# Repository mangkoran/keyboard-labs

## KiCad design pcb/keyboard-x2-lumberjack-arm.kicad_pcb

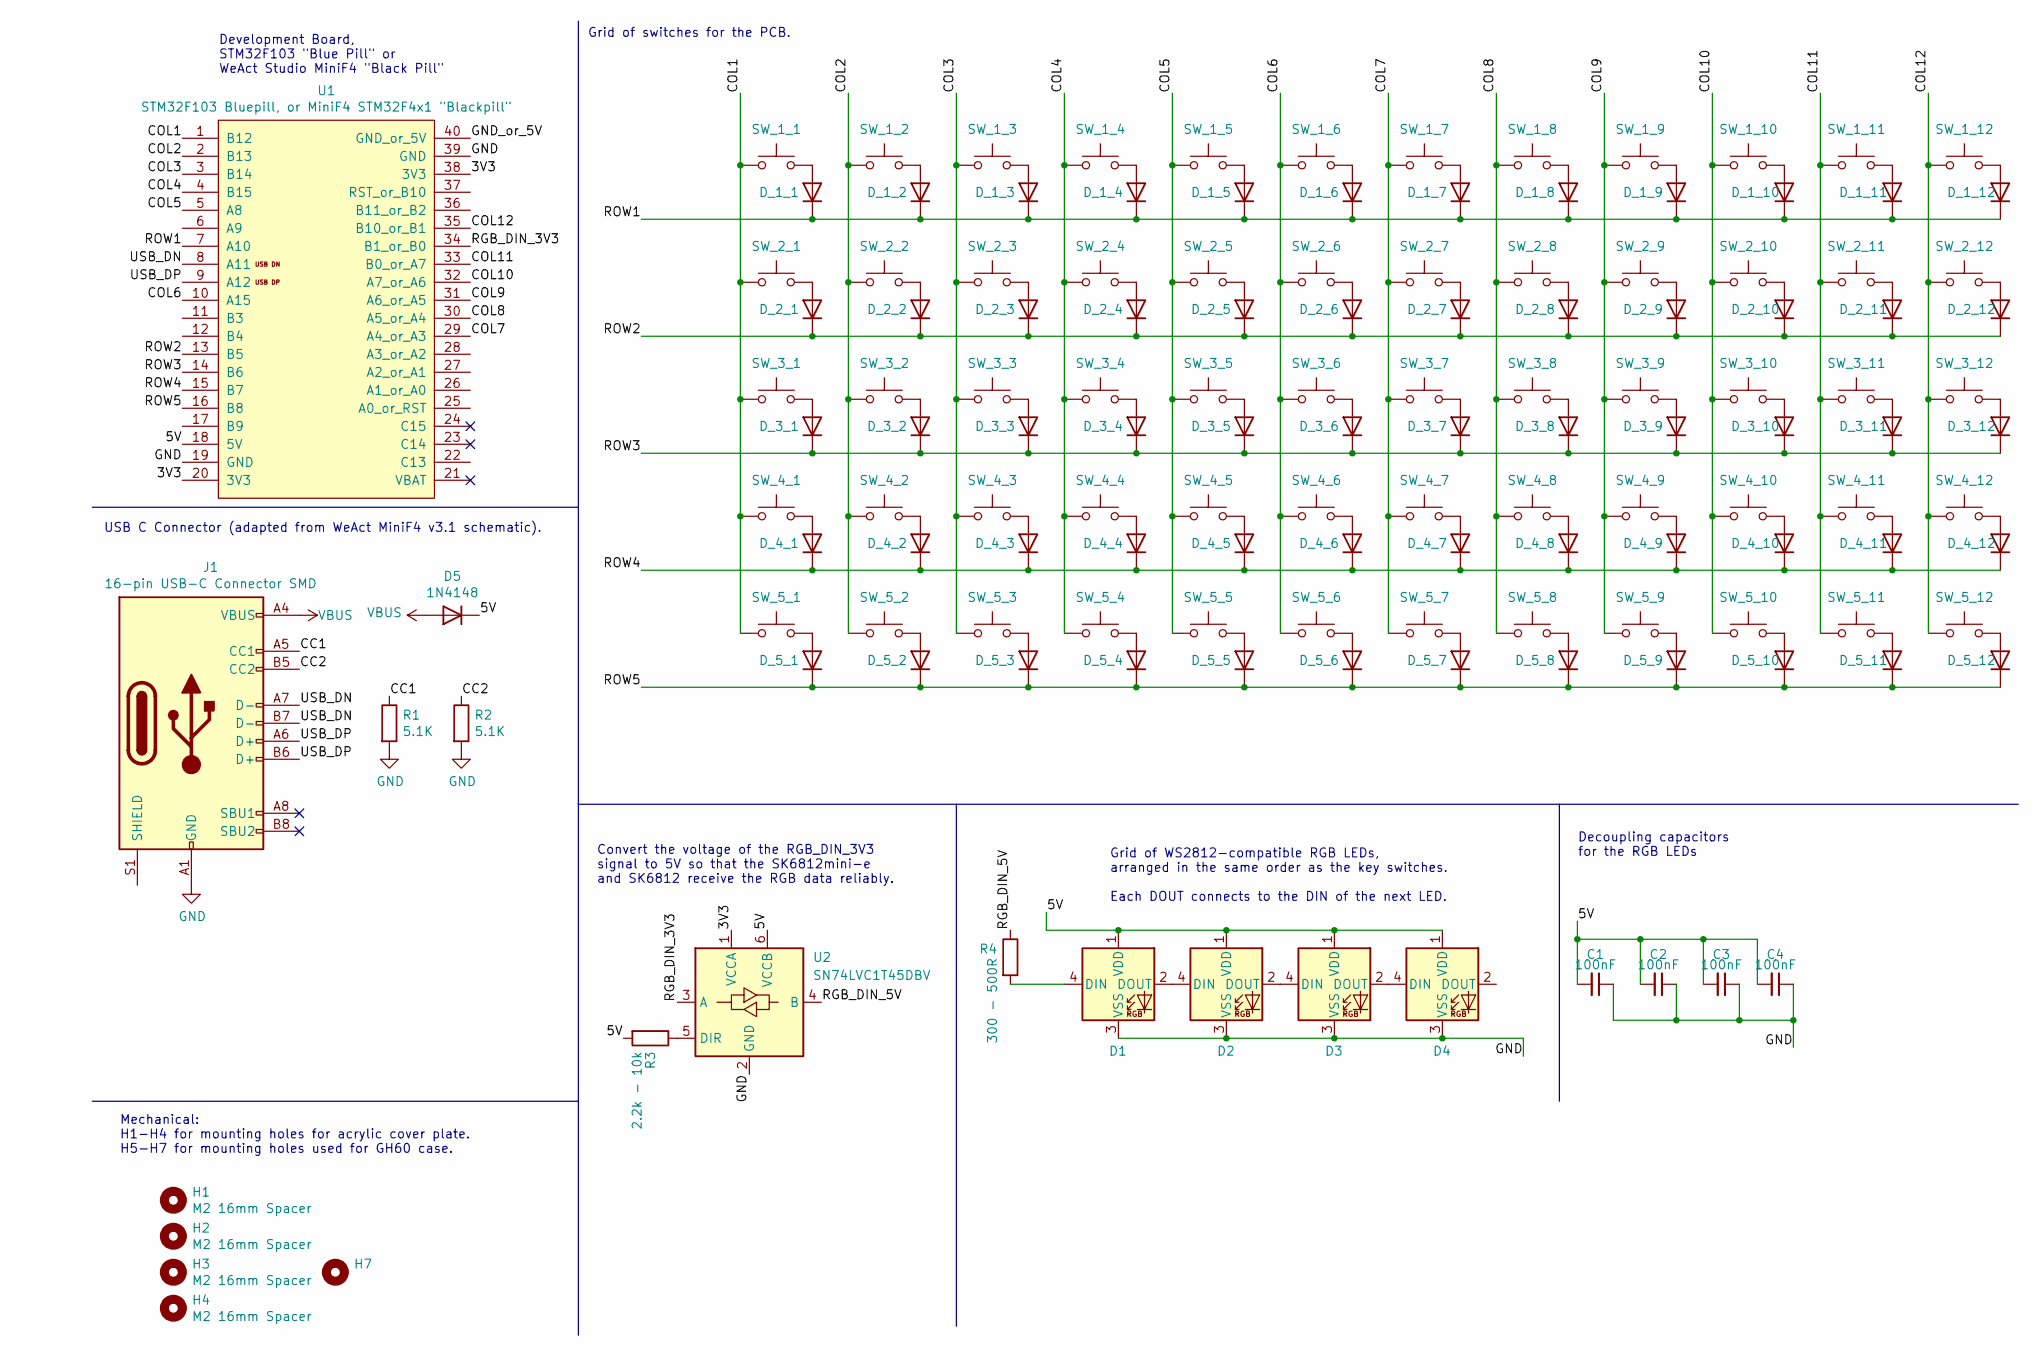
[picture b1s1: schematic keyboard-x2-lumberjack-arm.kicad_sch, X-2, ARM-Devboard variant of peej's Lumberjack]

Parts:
C1, C2, C3, C4: 100nF; C_0805_2012Metric_Pad1.18x1.45mm_HandSolder_Dual
D1, D2, D3, D4: SK6812; LED_WS2812B_PLCC4_5.0x5.0mm_P3.2mm
D5: 1N4148; Diode-dual
D_1_1, D_1_2, D_1_3, D_1_4, D_1_5, D_1_6, D_1_7, D_1_8, D_1_9, D_1_10, D_1_11, D_1_12, D_2_1, D_2_2, D_2_3, D_2_4, D_2_5, D_2_6, D_2_7, D_2_8, D_2_9, D_2_10, D_2_11, D_2_12, D_3_1, D_3_2, D_3_3, D_3_4, D_3_5, D_3_6, D_3_7, D_3_8, D_3_9, D_3_10, D_3_11, D_3_12, D_4_1, D_4_2, D_4_3, D_4_4, D_4_5, D_4_6, D_4_7, D_4_8, D_4_9, D_4_10, D_4_11, D_4_12, D_5_1, D_5_2, D_5_3, D_5_4, D_5_5, D_5_6, D_5_7, D_5_8, D_5_9, D_5_10, D_5_11, D_5_12: 1N4148; Diode-dual
H1, H2, H3, H4: M2 16mm Spacer; MountingHole_2.2mm_M2_DIN965_Pad
H7: H_M2_Spacer_Hole
J1: 16-pin USB-C Connector SMD; USB_C_Receptacle_XKB_U262-16XN-4BVC11
R1, R2: 5.1K; Resistor-Hybrid
R3: 2.2k - 10k; Resistor-Hybrid
R4: 300 - 500R; Resistor-Hybrid
SW_1_1, SW_1_2, SW_1_3, SW_1_4, SW_1_5, SW_1_6, SW_1_7, SW_1_8, SW_1_9, SW_1_10, SW_1_11, SW_1_12, SW_2_1, SW_2_2, SW_2_3, SW_2_4, SW_2_5, SW_2_6, SW_2_7, SW_2_8, SW_2_9, SW_2_10, SW_2_11, SW_2_12, SW_3_1, SW_3_2, SW_3_3, SW_3_4, SW_3_5, SW_3_6, SW_3_7, SW_3_8, SW_3_9, SW_3_10, SW_3_11, SW_3_12, SW_4_1, SW_4_2, SW_4_3, SW_4_4, SW_4_5, SW_4_6, SW_4_7, SW_4_8, SW_4_9, SW_4_10, SW_4_11, SW_4_12, SW_5_1, SW_5_2, SW_5_3, SW_5_4, SW_5_5, SW_5_6, SW_5_7, SW_5_8, SW_5_9, SW_5_10, SW_5_11, SW_5_12: MX Hotswap; MXOnly-1U-Hotswap-180
U1: STM32F103 Bluepill, or MiniF4 STM32F4x1 "Blackpil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; DIP-40_W15.24mm_Socket
U2: SN74LVC1T45DBV; SOT-23-6_Handsoldering

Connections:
/3V3: U1.20 (3V3), U1.38 (3V3), U2.1 (VCCA)
/5V: C1.2, C2.2, C3.2, C4.2, D1.1 (VDD), D2.1 (VDD), D3.1 (VDD), D4.1 (VDD), D5.1 (K), R3.2, U1.18 (5V), U2.6 (VCCB)
/CC1: J1.A5 (CC1), R1.1
/CC2: J1.B5 (CC2), R2.1
/COL1: SW_1_1.1, SW_2_1.1, SW_3_1.1, SW_4_1.1, SW_5_1.1, U1.1 (B12)
/COL2: SW_1_2.1, SW_2_2.1, SW_3_2.1, SW_4_2.1, SW_5_2.1, U1.2 (B13)
/COL3: SW_1_3.1, SW_2_3.1, SW_3_3.1, SW_4_3.1, SW_5_3.1, U1.3 (B14)
/COL4: SW_1_4.1, SW_2_4.1, SW_3_4.1, SW_4_4.1, SW_5_4.1, U1.4 (B15)
/COL5: SW_1_5.1, SW_2_5.1, SW_3_5.1, SW_4_5.1, SW_5_5.1, U1.5 (A8)
/COL6: SW_1_6.1, SW_2_6.1, SW_3_6.1, SW_4_6.1, SW_5_6.1, U1.10 (A15)
/COL7: SW_1_7.1, SW_2_7.1, SW_3_7.1, SW_4_7.1, SW_5_7.1, U1.29 (A4_or_A3)
/COL8: SW_1_8.1, SW_2_8.1, SW_3_8.1, SW_4_8.1, SW_5_8.1, U1.30 (A5_or_A4)
/COL9: SW_1_9.1, SW_2_9.1, SW_3_9.1, SW_4_9.1, SW_5_9.1, U1.31 (A6_or_A5)
/COL10: SW_1_10.1, SW_2_10.1, SW_3_10.1, SW_4_10.1, SW_5_10.1, U1.32 (A7_or_A6)
/COL11: SW_1_11.1, SW_2_11.1, SW_3_11.1, SW_4_11.1, SW_5_11.1, U1.33 (B0_or_A7)
/COL12: SW_1_12.1, SW_2_12.1, SW_3_12.1, SW_4_12.1, SW_5_12.1, U1.35 (B10_or_B1)
/GND_or_5V: U1.40 (GND_or_5V)
/RGB_DIN_3V3: U1.34 (B1_or_B0), U2.3 (A)
/RGB_DIN_5V: R4.1, U2.4 (B)
/ROW1: D_1_1.1 (K), D_1_2.1 (K), D_1_3.1 (K), D_1_4.1 (K), D_1_5.1 (K), D_1_6.1 (K), D_1_7.1 (K), D_1_8.1 (K), D_1_9.1 (K), D_1_10.1 (K), D_1_11.1 (K), D_1_12.1 (K), U1.7 (A10)
/ROW2: D_2_1.1 (K), D_2_2.1 (K), D_2_3.1 (K), D_2_4.1 (K), D_2_5.1 (K), D_2_6.1 (K), D_2_7.1 (K), D_2_8.1 (K), D_2_9.1 (K), D_2_10.1 (K), D_2_11.1 (K), D_2_12.1 (K), U1.13 (B5)
/ROW3: D_3_1.1 (K), D_3_2.1 (K), D_3_3.1 (K), D_3_4.1 (K), D_3_5.1 (K), D_3_6.1 (K), D_3_7.1 (K), D_3_8.1 (K), D_3_9.1 (K), D_3_10.1 (K), D_3_11.1 (K), D_3_12.1 (K), U1.14 (B6)
/ROW4: D_4_1.1 (K), D_4_2.1 (K), D_4_3.1 (K), D_4_4.1 (K), D_4_5.1 (K), D_4_6.1 (K), D_4_7.1 (K), D_4_8.1 (K), D_4_9.1 (K), D_4_10.1 (K), D_4_11.1 (K), D_4_12.1 (K), U1.15 (B7)
/ROW5: D_5_1.1 (K), D_5_2.1 (K), D_5_3.1 (K), D_5_4.1 (K), D_5_5.1 (K), D_5_6.1 (K), D_5_7.1 (K), D_5_8.1 (K), D_5_9.1 (K), D_5_10.1 (K), D_5_11.1 (K), D_5_12.1 (K), U1.16 (B8)
/USB_DN: J1.A7 (D-), J1.B7 (D-), U1.8 (A11)
/USB_DP: J1.A6 (D+), J1.B6 (D+), U1.9 (A12)
GND: C1.1, C2.1, C3.1, C4.1, D1.3 (VSS), D2.3 (VSS), D3.3 (VSS), D4.3 (VSS), J1.A1 (GND), J1.A12 (GND), J1.B1 (GND), J1.B12 (GND), R1.2, R2.2, U1.19 (GND), U1.39 (GND), U2.2 (GND)
unnamed: D1.2 (DOUT), D2.4 (DIN)
unnamed: D1.4 (DIN), R4.2
unnamed: D2.2 (DOUT), D3.4 (DIN)
unnamed: D3.2 (DOUT), D4.4 (DIN)
unnamed: D_1_1.2 (A), SW_1_1.2
unnamed: D_1_2.2 (A), SW_1_2.2
unnamed: D_1_3.2 (A), SW_1_3.2
unnamed: D_1_4.2 (A), SW_1_4.2
unnamed: D_1_5.2 (A), SW_1_5.2
unnamed: D_1_6.2 (A), SW_1_6.2
unnamed: D_1_7.2 (A), SW_1_7.2
unnamed: D_1_8.2 (A), SW_1_8.2
unnamed: D_1_9.2 (A), SW_1_9.2
unnamed: D_1_10.2 (A), SW_1_10.2
unnamed: D_1_11.2 (A), SW_1_11.2
unnamed: D_1_12.2 (A), SW_1_12.2
unnamed: D_2_1.2 (A), SW_2_1.2
unnamed: D_2_2.2 (A), SW_2_2.2
unnamed: D_2_3.2 (A), SW_2_3.2
unnamed: D_2_4.2 (A), SW_2_4.2
unnamed: D_2_5.2 (A), SW_2_5.2
unnamed: D_2_6.2 (A), SW_2_6.2
unnamed: D_2_7.2 (A), SW_2_7.2
unnamed: D_2_8.2 (A), SW_2_8.2
unnamed: D_2_9.2 (A), SW_2_9.2
unnamed: D_2_10.2 (A), SW_2_10.2
unnamed: D_2_11.2 (A), SW_2_11.2
unnamed: D_2_12.2 (A), SW_2_12.2
unnamed: D_3_1.2 (A), SW_3_1.2
unnamed: D_3_2.2 (A), SW_3_2.2
unnamed: D_3_3.2 (A), SW_3_3.2
unnamed: D_3_4.2 (A), SW_3_4.2
unnamed: D_3_5.2 (A), SW_3_5.2
unnamed: D_3_6.2 (A), SW_3_6.2
unnamed: D_3_7.2 (A), SW_3_7.2
unnamed: D_3_8.2 (A), SW_3_8.2
unnamed: D_3_9.2 (A), SW_3_9.2
unnamed: D_3_10.2 (A), SW_3_10.2
unnamed: D_3_11.2 (A), SW_3_11.2
unnamed: D_3_12.2 (A), SW_3_12.2
unnamed: D_4_1.2 (A), SW_4_1.2
unnamed: D_4_2.2 (A), SW_4_2.2
unnamed: D_4_3.2 (A), SW_4_3.2
unnamed: D_4_4.2 (A), SW_4_4.2
unnamed: D_4_5.2 (A), SW_4_5.2
unnamed: D_4_6.2 (A), SW_4_6.2
unnamed: D_4_7.2 (A), SW_4_7.2
unnamed: D_4_8.2 (A), SW_4_8.2
unnamed: D_4_9.2 (A), SW_4_9.2
unnamed: D_4_10.2 (A), SW_4_10.2
unnamed: D_4_11.2 (A), SW_4_11.2
unnamed: D_4_12.2 (A), SW_4_12.2
unnamed: D_5_1.2 (A), SW_5_1.2
unnamed: D_5_2.2 (A), SW_5_2.2
unnamed: D_5_3.2 (A), SW_5_3.2
unnamed: D_5_4.2 (A), SW_5_4.2
unnamed: D_5_5.2 (A), SW_5_5.2
unnamed: D_5_6.2 (A), SW_5_6.2
unnamed: D_5_7.2 (A), SW_5_7.2
unnamed: D_5_8.2 (A), SW_5_8.2
unnamed: D_5_9.2 (A), SW_5_9.2
unnamed: D_5_10.2 (A), SW_5_10.2
unnamed: D_5_11.2 (A), SW_5_11.2
unnamed: D_5_12.2 (A), SW_5_12.2
unnamed: R3.1, U2.5 (DIR)
VBUS: D5.2 (A), J1.A4 (VBUS), J1.A9 (VBUS), J1.B4 (VBUS), J1.B9 (VBUS)

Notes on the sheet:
Convert the voltage of the RGB_DIN_3V3 signal to 5V so that the SK6812mini-e and SK6812 receive the RGB data reliably.
Mechanical: H1-H4 for mounting holes for acrylic cover plate. H5-H7 for mounting holes used for GH60 case.
USB C Connector (adapted from WeAct MiniF4 v3.1 schematic).
Development Board, STM32F103 "Blue Pill" or WeAct Studio MiniF4 "Black Pill"
Grid of WS2812-compatible RGB LEDs, arranged in the same order as the key switches. Each DOUT connects to the DIN of the next LED.
Decoupling capacitors for the RGB LEDs
Grid of switches for the PCB.

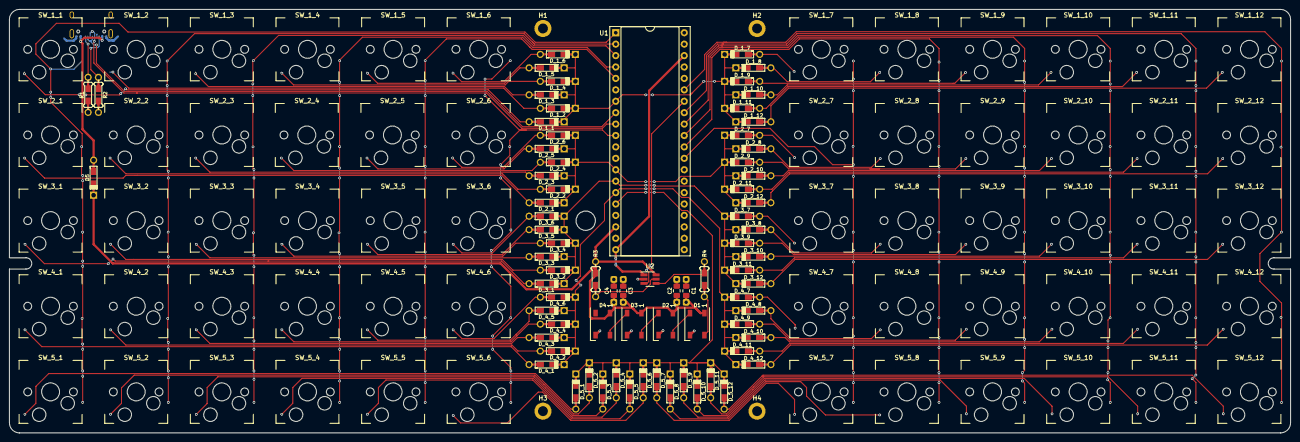
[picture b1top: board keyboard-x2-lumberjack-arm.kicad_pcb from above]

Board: 2 copper layers, 285.0 x 94.2 mm, 141 parts (1 on the bottom side), 92 nets.

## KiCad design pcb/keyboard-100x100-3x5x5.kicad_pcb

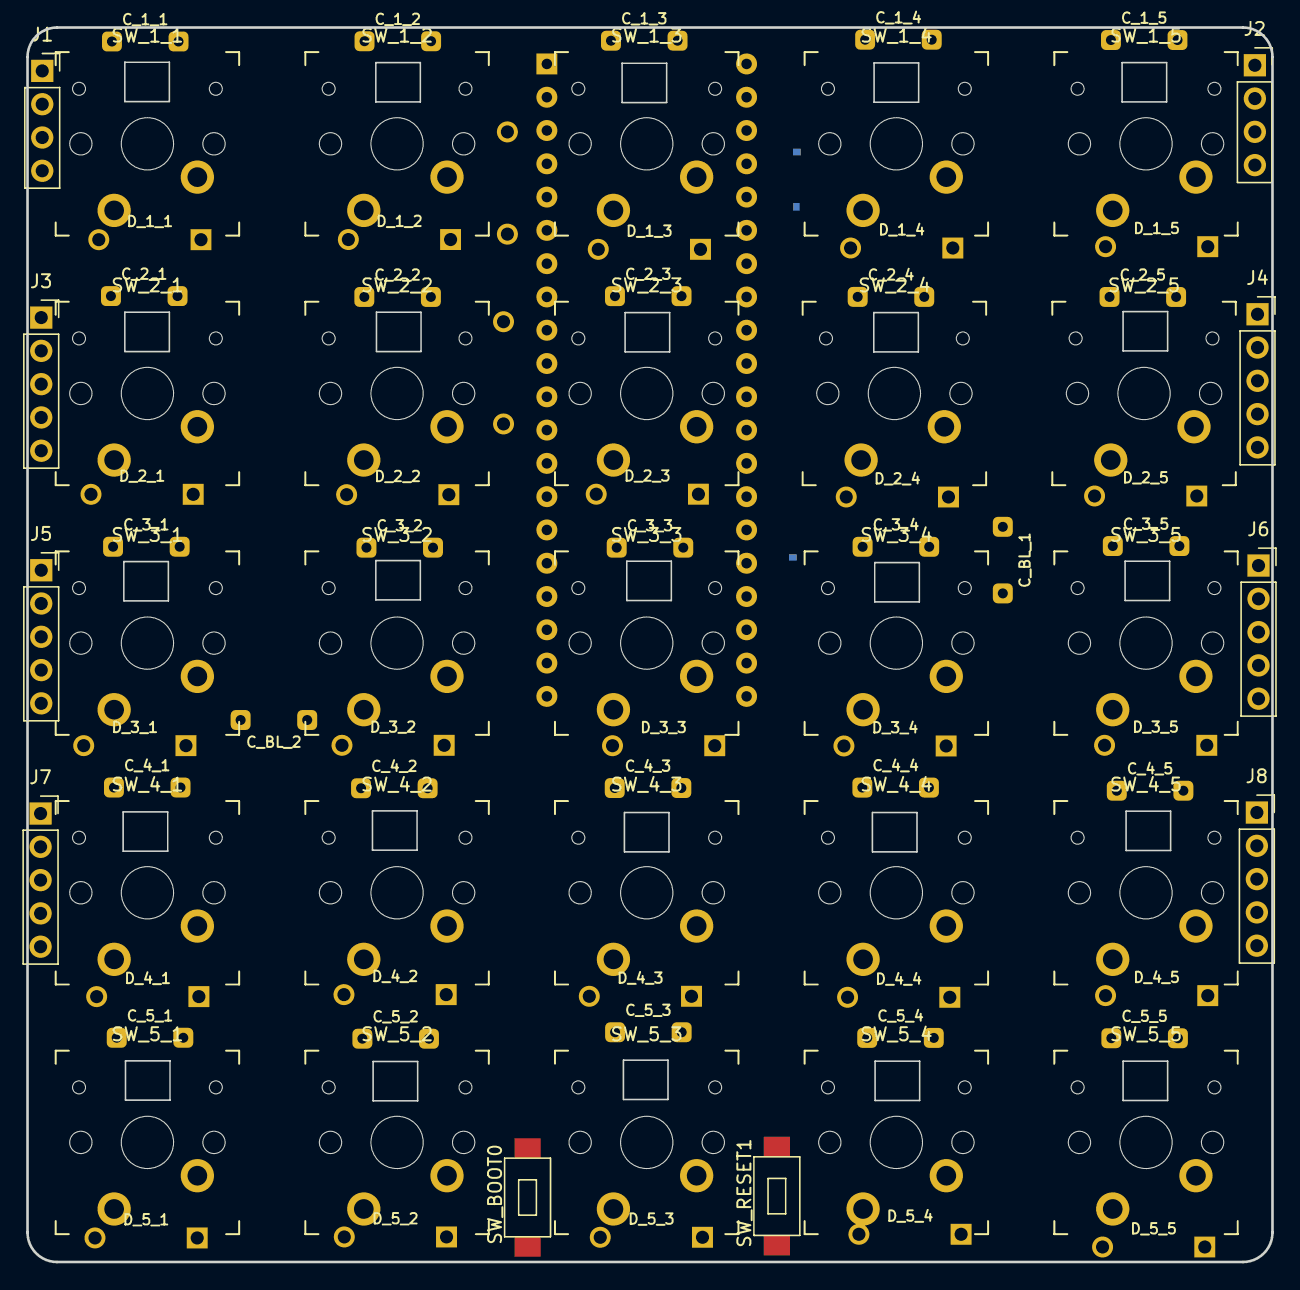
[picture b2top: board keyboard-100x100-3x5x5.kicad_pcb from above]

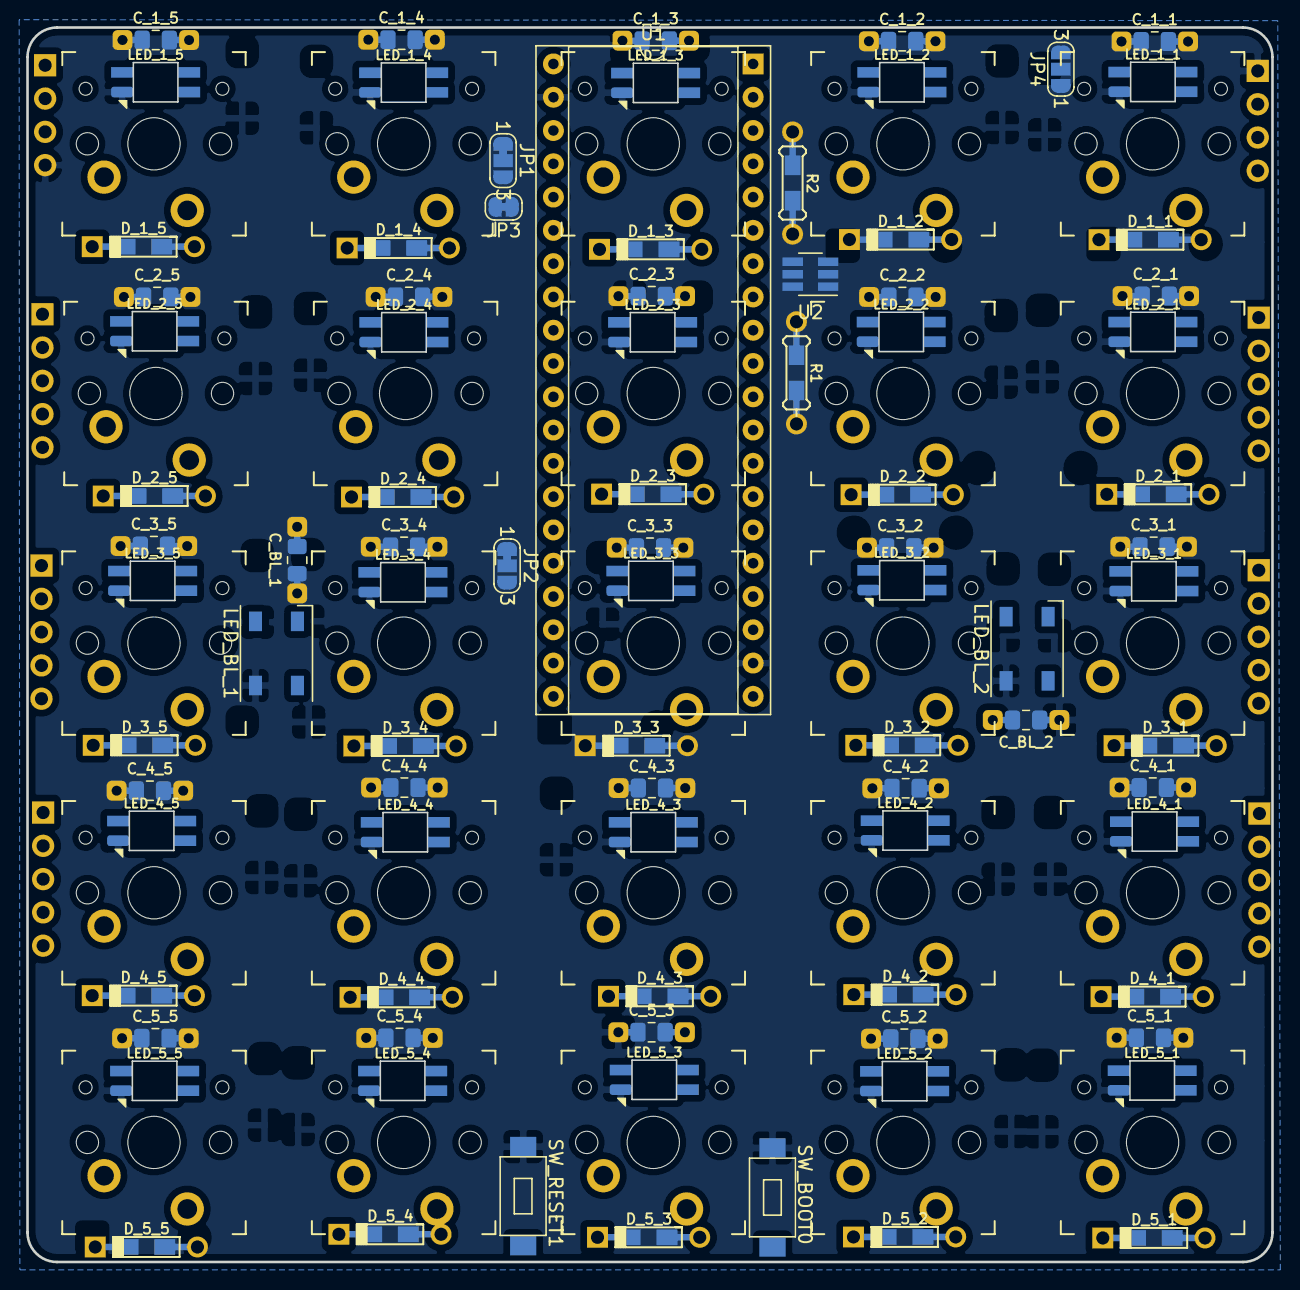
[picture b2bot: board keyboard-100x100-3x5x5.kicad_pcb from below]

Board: 2 copper layers, 95.0 x 94.2 mm, 126 parts (86 on the bottom side), 88 nets, no tracks yet.

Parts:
C_1_1, C_1_2, C_1_3, C_1_4, C_1_5, C_2_1, C_2_2, C_2_3, C_2_4, C_2_5, C_3_1, C_3_2, C_3_3, C_3_4, C_3_5, C_4_1, C_4_2, C_4_3, C_4_4, C_4_5, C_5_1, C_5_2, C_5_3, C_5_4, C_5_5: 100nF; C_0805_2012Metric_Pad1.18x1.45mm_HandSolder_Dual
C_BL_1, C_BL_2: 100nF; C_0805_2012Metric_Pad1.18x1.45mm_HandSolder_Dual
D_1_1, D_1_2, D_1_3, D_1_4, D_1_5, D_2_1, D_2_2, D_2_3, D_2_4, D_2_5, D_3_1, D_3_2, D_3_3, D_3_4, D_3_5, D_4_1, D_4_2, D_4_3, D_4_4, D_4_5, D_5_1, D_5_2, D_5_3, D_5_4, D_5_5: D; Diode-dual
H1, H2, H3, H4: MountingHole; Bumpon_3M_F0502
J1, J2: Conn_01x04_Female; PinSocket_1x04_P2.54mm_Vertical
J3, J4, J5, J6, J7, J8: Conn_01x05_Female; PinSocket_1x05_P2.54mm_Vertical
JP1, JP2: SolderJumper_3_Bridged12; SolderJumper-3_P1.3mm_Bridged12_RoundedPad1.0x1.5mm_NumberL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
JP3: SolderJumper_2_Bridged; SolderJumper-2_P1.3mm_Bridged_RoundedPad1.0x1.5mm
JP4: SolderJumper_3_Open; SolderJumper-3_P1.3mm_Open_RoundedPad1.0x1.5mm_NumberLabels
LED_1_1, LED_1_2, LED_1_3, LED_1_4, LED_1_5, LED_2_1, LED_2_2, LED_2_3, LED_2_4, LED_2_5, LED_3_1, LED_3_2, LED_3_3, LED_3_4, LED_3_5, LED_4_1, LED_4_2, LED_4_3, LED_4_4, LED_4_5, LED_5_1, LED_5_2, LED_5_3, LED_5_4, LED_5_5: WS2812B; SK6812-MINI-E
LED_BL_1, LED_BL_2: WS2812B; LED_SK6812_PLCC4_5.0x5.0mm_P3.2mm
R1: 2.2k - 10k; Resistor-Hybrid
R2: 300 - 500R; Resistor-Hybrid
SW_1_1, SW_1_2, SW_1_3, SW_1_4, SW_1_5, SW_2_1, SW_2_2, SW_2_3, SW_2_4, SW_2_5, SW_3_1, SW_3_2, SW_3_3, SW_3_4, SW_3_5, SW_4_1, SW_4_2, SW_4_3, SW_4_4, SW_4_5, SW_5_1, SW_5_2, SW_5_3, SW_5_4, SW_5_5: SW_Push; SW_MX_SK6812mini-e
SW_BOOT0: SW_Push; SW_Push_SPST_3x6mm
SW_RESET1: SW_Push; SW_Push_SPST_3x6mm
U1: BluePill_or_MiniF4_DIP40; DIP-40_W15.24mm_Socket_Flipped
U2: SN74LVC1T45DBV; SOT-23-6_Handsoldering

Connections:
/3V3: U1.20, U1.38, U2.1
/5V: C_1_1.2, C_1_2.2, C_1_3.2, C_1_4.2, C_1_5.2, C_2_1.2, C_2_2.2, C_2_3.2, C_2_4.2, C_2_5.2, C_3_1.2, C_3_2.2, C_3_3.2, C_3_4.2, C_3_5.2, C_4_1.2, C_4_2.2, C_4_3.2, C_4_4.2, C_4_5.2, C_5_1.2, C_5_2.2, C_5_3.2, C_5_4.2, C_5_5.2, C_BL_1.2, C_BL_2.2, J1.2, J2.3, LED_1_1.1, LED_1_2.1, LED_1_3.1, LED_1_4.1, LED_1_5.1, LED_2_1.1, LED_2_2.1, LED_2_3.1, LED_2_4.1, LED_2_5.1, LED_3_1.1, LED_3_2.1, LED_3_3.1, LED_3_4.1, LED_3_5.1, LED_4_1.1, LED_4_2.1, LED_4_3.1, LED_4_4.1, LED_4_5.1, LED_5_1.1, LED_5_2.1, LED_5_3.1, LED_5_4.1, LED_5_5.1, LED_BL_1.1, LED_BL_2.1, R1.2, U1.18, U2.6
/BOOT0: JP3.2, SW_BOOT0.1
/COL1: J5.5, J8.1, SW_1_1.1, SW_2_1.1, SW_3_1.1, SW_4_1.1, SW_5_1.1, U1.10
/COL2: J5.4, J8.2, SW_1_2.1, SW_2_2.1, SW_3_2.1, SW_4_2.1, SW_5_2.1, U1.29
/COL3: J5.3, J8.3, SW_1_3.1, SW_2_3.1, SW_3_3.1, SW_4_3.1, SW_5_3.1, U1.30
/COL4: J5.2, J8.4, SW_1_4.1, SW_2_4.1, SW_3_4.1, SW_4_4.1, SW_5_4.1, U1.31
/COL5: J5.1, J8.5, SW_1_5.1, SW_2_5.1, SW_3_5.1, SW_4_5.1, SW_5_5.1, U1.32
/GND: C_1_1.1, C_1_2.1, C_1_3.1, C_1_4.1, C_1_5.1, C_2_1.1, C_2_2.1, C_2_3.1, C_2_4.1, C_2_5.1, C_3_1.1, C_3_2.1, C_3_3.1, C_3_4.1, C_3_5.1, C_4_1.1, C_4_2.1, C_4_3.1, C_4_4.1, C_4_5.1, C_5_1.1, C_5_2.1, C_5_3.1, C_5_4.1, C_5_5.1, C_BL_1.1, C_BL_2.1, J1.1, J2.4, LED_1_1.3, LED_1_2.3, LED_1_3.3, LED_1_4.3, LED_1_5.3, LED_2_1.3, LED_2_2.3, LED_2_3.3, LED_2_4.3, LED_2_5.3, LED_3_1.3, LED_3_2.3, LED_3_3.3, LED_3_4.3, LED_3_5.3, LED_4_1.3, LED_4_2.3, LED_4_3.3, LED_4_4.3, LED_4_5.3, LED_5_1.3, LED_5_2.3, LED_5_3.3, LED_5_4.3, LED_5_5.3, LED_BL_1.3, LED_BL_2.3, SW_BOOT0.2, SW_RESET1.2, U1.19, U1.39, U2.2
/LED_1_IN: JP4.2, LED_1_1.4
/LED_2_IN: LED_1_5.2, LED_2_1.4
/LED_3_IN: LED_2_5.2, LED_3_1.4
/LED_4_IN: LED_3_5.2, LED_4_1.4
/LED_5_IN: LED_4_5.2, LED_5_1.4
/LED_BL_IN: LED_5_5.2, LED_BL_1.4
/NC_or_BOOT0: JP3.1, U1.36
/NEXT_COL1: J6.1, U1.35
/NEXT_COL2: J6.2, U1.33
/NEXT_COL3: J6.3, U1.28
/NEXT_COL4: J6.4, U1.27
/NEXT_COL5: J6.5, U1.26
/PREV_COL1: J7.5, U1.1
/PREV_COL2: J7.4, U1.2
/PREV_COL3: J7.3, U1.3
/PREV_COL4: J7.2, U1.4
/PREV_COL5: J7.1, U1.5
/RESET: JP1.3, JP2.1, SW_RESET1.1
/RESET_or_X: JP1.2, U1.37
/RGB_DATA_IN: J1.3, JP4.1
/RGB_DATA_OUT: J2.2, LED_BL_2.2
/RGB_DATA_START_IN: J2.1, JP4.3
/RGB_DATA_START_OUT: J1.4, R2.2
/RGB_DIN_3V3: U1.34, U2.3
/RGB_DIN_5V: R2.1, U2.4
/ROW1: D_1_1.1, D_1_2.1, D_1_3.1, D_1_4.1, D_1_5.1, J3.5, J4.1, U1.7
/ROW2: D_2_1.1, D_2_2.1, D_2_3.1, D_2_4.1, D_2_5.1, J3.4, J4.2, U1.13
/ROW3: D_3_1.1, D_3_2.1, D_3_3.1, D_3_4.1, D_3_5.1, J3.3, J4.3, U1.14
/ROW4: D_4_1.1, D_4_2.1, D_4_3.1, D_4_4.1, D_4_5.1, J3.2, J4.4, U1.15
/ROW5: D_5_1.1, D_5_2.1, D_5_3.1, D_5_4.1, D_5_5.1, J3.1, J4.5, U1.16
/X: JP1.1, JP2.3
/X_or_RESET: JP2.2, U1.25
unnamed: D_1_1.2, SW_1_1.2
unnamed: D_1_2.2, SW_1_2.2
unnamed: D_1_3.2, SW_1_3.2
unnamed: D_1_4.2, SW_1_4.2
unnamed: D_1_5.2, SW_1_5.2
unnamed: D_2_1.2, SW_2_1.2
unnamed: D_2_2.2, SW_2_2.2
unnamed: D_2_3.2, SW_2_3.2
unnamed: D_2_4.2, SW_2_4.2
unnamed: D_2_5.2, SW_2_5.2
unnamed: D_3_1.2, SW_3_1.2
unnamed: D_3_2.2, SW_3_2.2
unnamed: D_3_3.2, SW_3_3.2
unnamed: D_3_4.2, SW_3_4.2
unnamed: D_3_5.2, SW_3_5.2
unnamed: D_4_1.2, SW_4_1.2
unnamed: D_4_2.2, SW_4_2.2
unnamed: D_4_3.2, SW_4_3.2
unnamed: D_4_4.2, SW_4_4.2
unnamed: D_4_5.2, SW_4_5.2
unnamed: D_5_1.2, SW_5_1.2
unnamed: D_5_2.2, SW_5_2.2
unnamed: D_5_3.2, SW_5_3.2
unnamed: D_5_4.2, SW_5_4.2
unnamed: D_5_5.2, SW_5_5.2
unnamed: LED_1_1.2, LED_1_2.4
unnamed: LED_1_2.2, LED_1_3.4
unnamed: LED_1_3.2, LED_1_4.4
unnamed: LED_1_4.2, LED_1_5.4
unnamed: LED_2_1.2, LED_2_2.4
unnamed: LED_2_2.2, LED_2_3.4
unnamed: LED_2_3.2, LED_2_4.4
unnamed: LED_2_4.2, LED_2_5.4
unnamed: LED_3_1.2, LED_3_2.4
unnamed: LED_3_2.2, LED_3_3.4
unnamed: LED_3_3.2, LED_3_4.4
unnamed: LED_3_4.2, LED_3_5.4
unnamed: LED_4_1.2, LED_4_2.4
unnamed: LED_4_2.2, LED_4_3.4
unnamed: LED_4_3.2, LED_4_4.4
unnamed: LED_4_4.2, LED_4_5.4
unnamed: LED_5_1.2, LED_5_2.4
unnamed: LED_5_2.2, LED_5_3.4
unnamed: LED_5_3.2, LED_5_4.4
unnamed: LED_5_4.2, LED_5_5.4
unnamed: LED_BL_1.2, LED_BL_2.4
unnamed: R1.1, U2.5

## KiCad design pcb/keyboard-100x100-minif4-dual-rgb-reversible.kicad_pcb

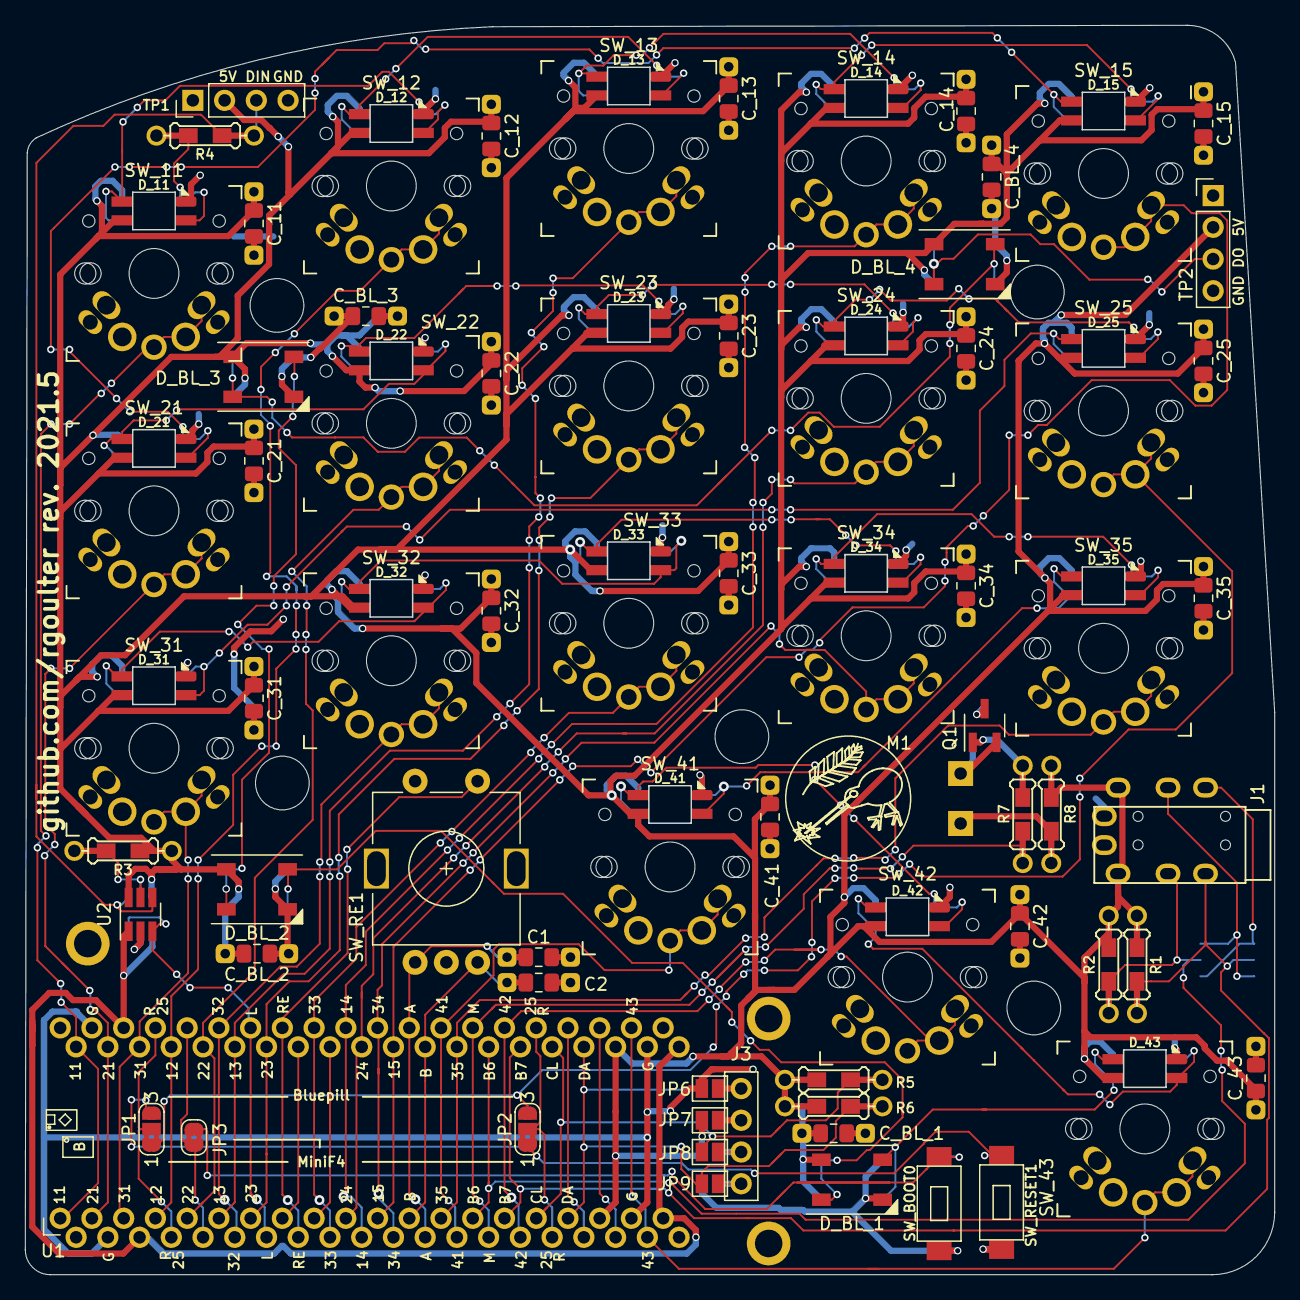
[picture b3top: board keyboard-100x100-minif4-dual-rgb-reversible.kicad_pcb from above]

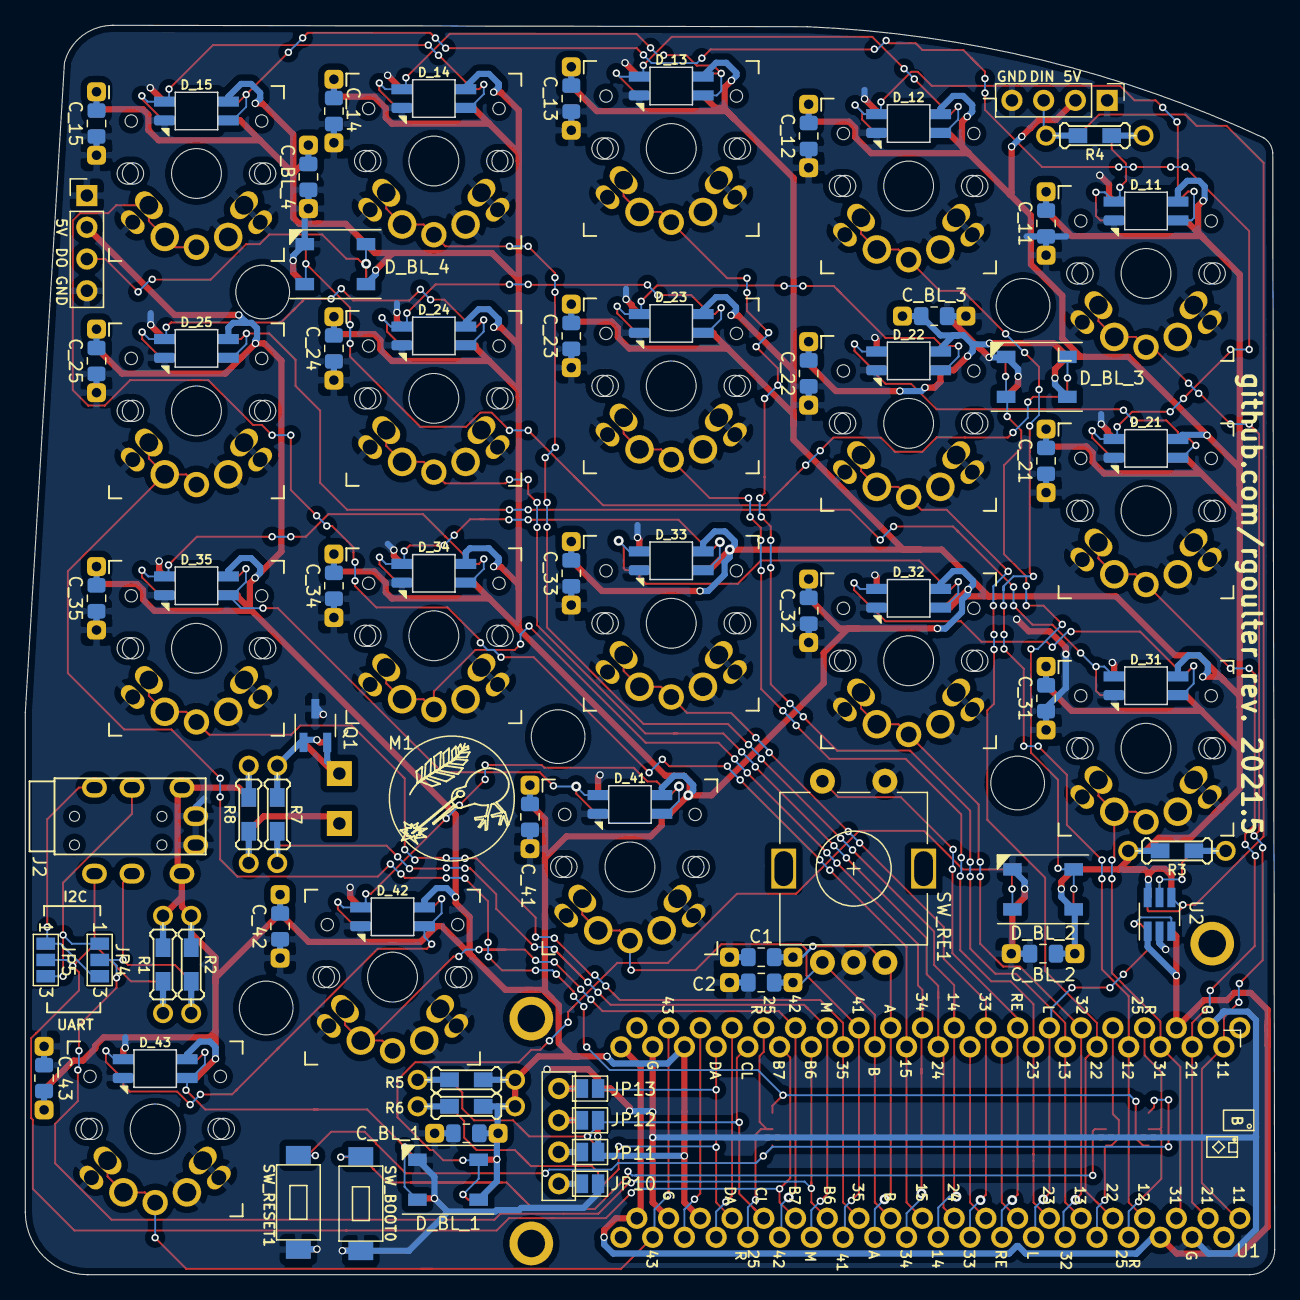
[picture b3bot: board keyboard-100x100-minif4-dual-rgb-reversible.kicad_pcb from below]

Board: 2 copper layers, 100.0 x 100.0 mm, 110 parts (51 on the bottom side), 69 nets.

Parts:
C1, C2: 100nF; C_0805_2012Metric_Pad1.18x1.45mm_HandSolder_Dual
C_11, C_12, C_13, C_14, C_15, C_21, C_22, C_23, C_24, C_25, C_31, C_32, C_33, C_34, C_35, C_41, C_42, C_43: 100nF; C_0805_2012Metric_Pad1.18x1.45mm_HandSolder_Dual
C_BL_1, C_BL_2, C_BL_3, C_BL_4: 100nF; C_0805_2012Metric_Pad1.18x1.45mm_HandSolder_Dual
D_11, D_12, D_13, D_14, D_15, D_21, D_22, D_23, D_24, D_25, D_31, D_32, D_33, D_34, D_35, D_41, D_42, D_43: WS2812B; SK6812-MINI-E_Reversible
D_BL_1, D_BL_2, D_BL_3, D_BL_4: SK6812; LED_SK6812_PLCC4_5.0x5.0mm_P3.2mm_Reversible
H1, H2, H3, H4, H5: MountingHole; Bumpon_3M_F0502
H6, H7, H8, H9, H10: MountingHole; H_M2_Spacer_Hole
H11, H12, H13: MountingHole; MountingHole_2.2mm_M2_ISO7380_Pad
J1, J2: TRRS; TRRS-PJ-320A
J3: Conn_01x04_Female; PinSocket_1x04_P2.54mm_Vertical
JP1, JP2: SolderJumper_3_Bridged12; SolderJumper-3_P1.3mm_Bridged2Bar12_RoundedPad1.0x1.5mm_Num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
JP3: SolderJumper_2_Bridged; SolderJumper-2_P1.3mm_Bridged2Bar_RoundedPad1.0x1.5mm
JP4, JP5: SolderJumper_3_Open; SolderJumper-3_P1.3mm_Open_Pad1.0x1.5mm_NumberLabels
JP6, JP7, JP8, JP9, JP10, JP11, JP12, JP13: SolderJumper_2_Open; SolderJumper-2_P1.3mm_Open_Pad1.0x1.5mm
M1: Motor_DC; Mini_DC_Motor
Q1: Q_NPN_BCE; SOT-23_Handsoldering_Reversible
R1, R2, R3, R5, R6: 2.2k - 10k; Resistor-Hybrid
R4: 300 - 500R; Resistor-Hybrid
R7, R8: 500R; Resistor-Hybrid
SW_11, SW_12, SW_13, SW_14, SW_15, SW_21, SW_22, SW_23, SW_24, SW_25, SW_31, SW_32, SW_33, SW_34, SW_35, SW_41, SW_42, SW_43: SW_Push; SW_MX_PG1350_reversible
SW_BOOT0: SW_Push; SW_Push_SPST_3x6mm
SW_RE1: Rotary_Encoder_Switch; RotaryEncoder_Alps_EC11E-Switch_Vertical_H20mm_Reversible
SW_RESET1: SW_Push; SW_Push_SPST_3x6mm
TP1, TP2: Conn_01x04_Female; PinHeader_1x04_P2.54mm_Vertical
U1: BluePill_or_MiniF4; DIP40_Reversible_ZigZag
U2: SN74LVC1T45DBV; SOT-23-6_Handsoldering_Reversible

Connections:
/3V3: U1.20, U1.23, U2.1
/5V: C_11.2, C_12.2, C_13.2, C_14.2, C_15.2, C_21.2, C_22.2, C_23.2, C_24.2, C_25.2, C_31.2, C_32.2, C_33.2, C_34.2, C_35.2, C_41.2, C_42.2, C_43.2, C_BL_1.1, C_BL_2.1, C_BL_3.1, C_BL_4.1, D_11.1, D_12.1, D_13.1, D_14.1, D_15.1, D_21.1, D_22.1, D_23.1, D_24.1, D_25.1, D_31.1, D_32.1, D_33.1, D_34.1, D_35.1, D_41.1, D_42.1, D_43.1, D_BL_1.3, D_BL_2.3, D_BL_3.3, D_BL_4.3, J1.2, J2.2, JP7.1, JP11.1, R1.1, R2.1, R3.2, R5.1, R6.1, R8.2, TP1.2, TP2.2, U1.18, U2.6
/BOOT0: JP3.2, SW_BOOT0.1
/DOUT_1: D_15.2, D_21.4
/DOUT_2: D_25.2, D_31.4
/DOUT_3: D_35.2, D_41.4
/DOUT_4: D_43.2, D_BL_1.2
/DOUT_BL: D_BL_4.4, TP2.3
/GND: C1.1, C2.1, C_11.1, C_12.1, C_13.1, C_14.1, C_15.1, C_21.1, C_22.1, C_23.1, C_24.1, C_25.1, C_31.1, C_32.1, C_33.1, C_34.1, C_35.1, C_41.1, C_42.1, C_43.1, C_BL_1.2, C_BL_2.2, C_BL_3.2, C_BL_4.2, D_11.3, D_12.3, D_13.3, D_14.3, D_15.3, D_21.3, D_22.3, D_23.3, D_24.3, D_25.3, D_31.3, D_32.3, D_33.3, D_34.3, D_35.3, D_41.3, D_42.3, D_43.3, D_BL_1.1, D_BL_2.1, D_BL_3.1, D_BL_4.1, J1.1, J2.1, JP6.1, JP10.1, Q1.3, SW_11.2, SW_12.2, SW_13.2, SW_14.2, SW_15.2, SW_21.2, SW_22.2, SW_23.2, SW_24.2, SW_25.2, SW_31.2, SW_32.2, SW_33.2, SW_34.2, SW_35.2, SW_41.2, SW_42.2, SW_43.2, SW_BOOT0.2, SW_RE1.C, SW_RE1.S2, SW_RESET1.2, TP1.1, TP1.4, TP2.1, TP2.4, U1.19, U1.22, U2.2
/MOTOR_GND: M1.2, Q1.2
/MOTOR_PWM: R7.1, U1.34
/NC_or_BOOT0: JP3.1, U1.25
/OLED_SCL: JP8.1, JP12.1, R5.2, U1.16
/OLED_SDA: JP9.1, JP13.1, R6.2, U1.17
/RESET: JP1.3, JP2.1, SW_RESET1.1
/RESET_or_SW25: JP1.2, U1.24
/RE_A: C1.2, SW_RE1.A, U1.32
/RE_B: C2.2, SW_RE1.B, U1.12
/RGB_DIN_3V3: U1.27, U2.3
/RGB_DIN_5V: R4.1, TP1.3, U2.4
/SCL_TX: J1.3, JP4.2, R2.2, U1.14
/SCL_TX_r: J2.3, JP4.1, JP5.3
/SDA_RX: J1.4, JP5.2, R1.2, U1.15
/SDA_RX_r: J2.4, JP4.3, JP5.1
/SW11: SW_11.1, U1.1
/SW12: SW_12.1, U1.4
/SW13: SW_13.1, U1.6
/SW14: SW_14.1, U1.30
/SW15: SW_15.1, U1.11
/SW21: SW_21.1, U1.2
/SW22: SW_22.1, U1.5
/SW23: SW_23.1, U1.7
/SW24: SW_24.1, U1.10
/SW25: JP1.1, JP2.3, SW_25.1
/SW25_or_RESET: JP2.2, U1.36
/SW31: SW_31.1, U1.3
/SW32: SW_32.1, U1.26
/SW33: SW_33.1, U1.29
/SW34: SW_34.1, U1.31
/SW35: SW_35.1, U1.13
/SW41: SW_41.1, U1.33
/SW42: SW_42.1, U1.35
/SW43: SW_43.1, U1.39
/SW_RE: SW_RE1.S1, U1.28
unnamed: D_11.2, D_12.4
unnamed: D_11.4, R4.2
unnamed: D_12.2, D_13.4
unnamed: D_13.2, D_14.4
unnamed: D_14.2, D_15.4
unnamed: D_21.2, D_22.4
unnamed: D_22.2, D_23.4
unnamed: D_23.2, D_24.4
unnamed: D_24.2, D_25.4
unnamed: D_31.2, D_32.4
unnamed: D_32.2, D_33.4
unnamed: D_33.2, D_34.4
unnamed: D_34.2, D_35.4
unnamed: D_41.2, D_42.4
unnamed: D_42.2, D_43.4
unnamed: D_BL_1.4, D_BL_2.2
unnamed: D_BL_2.4, D_BL_3.2
unnamed: D_BL_3.4, D_BL_4.2
unnamed: J3.1, JP6.2, JP13.2
unnamed: J3.2, JP7.2, JP12.2
unnamed: J3.3, JP8.2, JP11.2
unnamed: J3.4, JP9.2, JP10.2
unnamed: M1.1, R8.1
unnamed: Q1.1, R7.2
unnamed: R3.1, U2.5

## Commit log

2021-05-15 no one would ever use RUSTFLAGS and .cargo/config.
2021-06-03 wip; need some rerouting
2021-06-06 iterate
2021-06-07 mostly connected, but also very untidy
2021-06-07 and that
2021-06-08 pullup OLED CL/DA to simplify routing; adjust OLED JPs
2021-06-08 everything connected; albeit very untidy
2021-06-08 wip; move resistor pairs so they all look similar distance apart;
2021-06-09 technically everything connected
2021-06-09 remove all SW_xx traces; clean around H12
2021-06-09 wip, retracing
2021-06-09 retraced, but some still needs some tidying
2021-06-09 more tidying
2021-06-10 move Q1 RD
2021-06-10 move M1 RD
2021-06-10 adjust schematic
2021-12-03 [WIP] keyboard-x2-lumberjack-arm; unrouted
2021-12-04 Kicad: footprints: change to use SMD, Choc, MiniF4
2021-12-04 Kicad: adjust footprints to use 3D models for Bluepill, Through-Hole, MX
2021-12-04 Kicad: PCB: x-2: use edge-cuts, rather than NPTH that sit on board's edge
2021-12-04 Kicad: PCB: use 0.3mm via drill (via size 0.6mm) so that via >=0.15mm
    For PCB Fabrication manufacturer SmartPCB88
2022-02-04 chore: add 1U hotswap 180 rotated
2022-02-04 chore: add ai03's MX-Alps footprint lib
2022-02-04 feat: initial 1U hotswap implementation
2022-02-04 fix: update 1U hotswap footprint
2022-02-04 feat: 1U hotswap sw1-7 - sw1-12
2022-02-04 feat: 1U hotswap sw2-1 - sw2-12
2022-02-04 feat: 1U hotswap sw3-1 - sw3-12
2022-02-04 feat: 1U hotswap sw4-1 - sw4-12
2022-02-04 feat: 1U hotswap sw5-1 - sw5-12
2022-02-04 fix: unconnected pad
2022-02-04 fix: change switch symbol value to mx hotswap
2022-02-04 chore: tidy up routing
